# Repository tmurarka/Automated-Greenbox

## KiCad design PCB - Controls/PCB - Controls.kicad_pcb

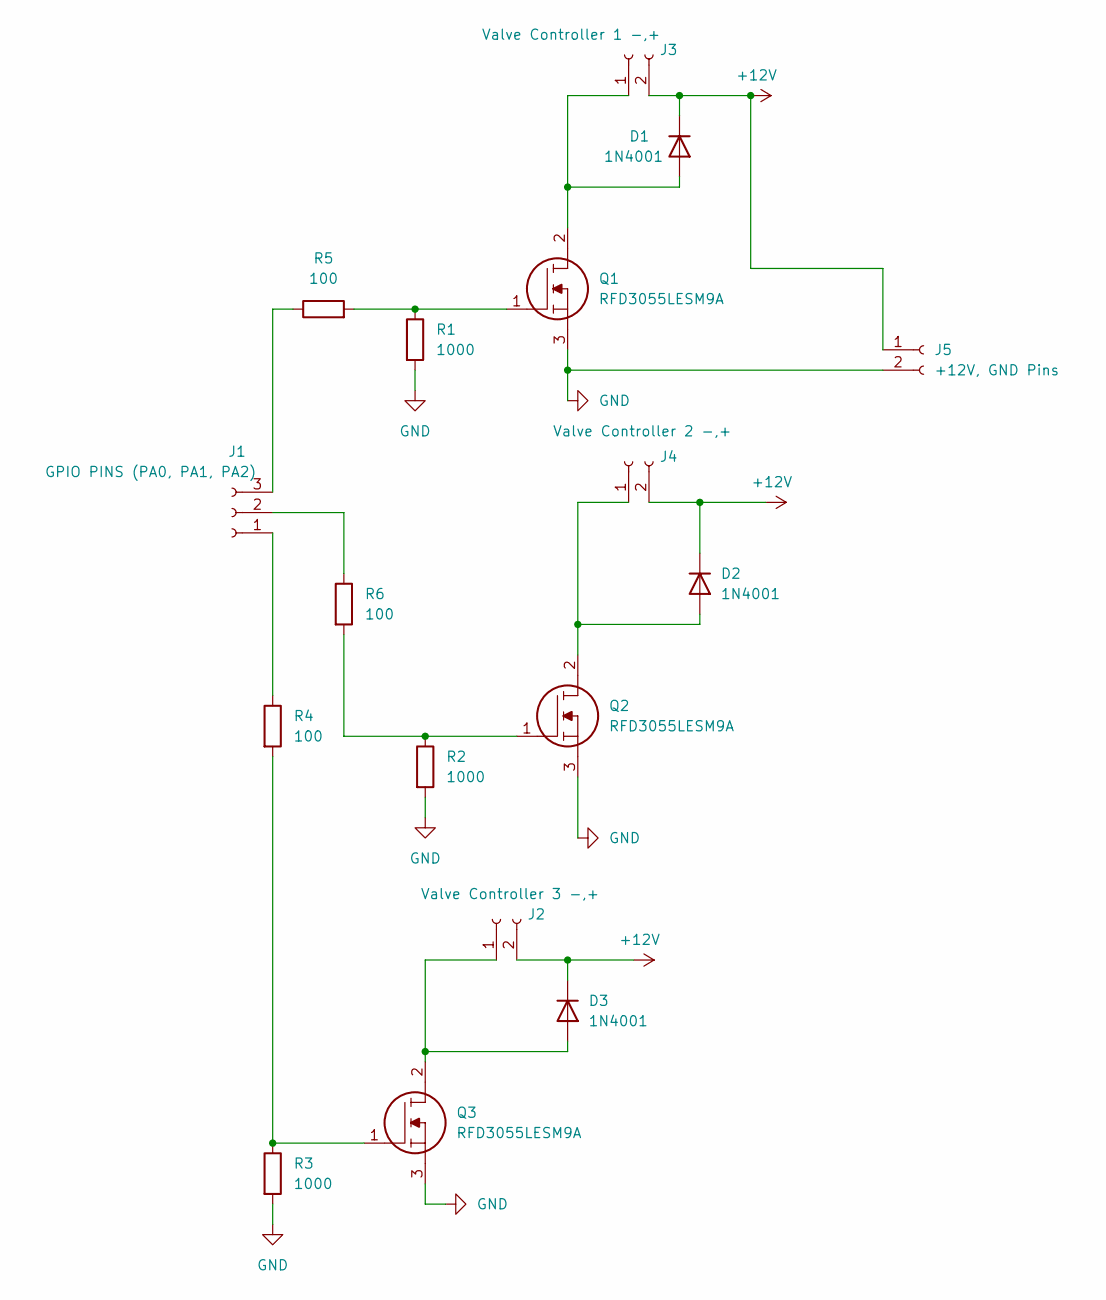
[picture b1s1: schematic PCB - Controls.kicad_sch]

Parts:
D1, D2, D3: 1N4001; D_DO-41_SOD81_P10.16mm_Horizontal
J1: GPIO PINS (PA0, PA1, PA2); PhoenixContact_MCV_1,5_3-G-3.81_1x03_P3.81mm_Vertical
J2: Valve Controller 3 -,+; PhoenixContact_MCV_1,5_2-G-3.81_1x02_P3.81mm_Vertical
J3: Valve Controller 1 -,+; PhoenixContact_MCV_1,5_2-G-3.81_1x02_P3.81mm_Vertical
J4: Valve Controller 2 -,+; PhoenixContact_MCV_1,5_2-G-3.81_1x02_P3.81mm_Vertical
J5: +12V, GND Pins; PhoenixContact_MCV_1,5_2-G-3.81_1x02_P3.81mm_Vertical
Q1, Q2, Q3: RFD3055LESM9A; FQD1N80TM; Mouser Part Number 512-RFD3055LESM9A
R1, R2, R3: 1000; R_Axial_DIN0204_L3.6mm_D1.6mm_P1.90mm_Vertical
R4, R5, R6: 100; R_Axial_DIN0204_L3.6mm_D1.6mm_P1.90mm_Vertical

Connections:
+12V: D1.1 (K), D2.1 (K), D3.1 (K), J2.2, J3.2, J4.2, J5.1
GND: J5.2, Q1.3, Q2.3, Q3.3, R1.2, R2.2, R3.2
unnamed: D1.2 (A), J3.1, Q1.2
unnamed: D2.2 (A), J4.1, Q2.2
unnamed: D3.2 (A), J2.1, Q3.2
unnamed: J1.1, R4.1
unnamed: J1.2, R6.1
unnamed: J1.3, R5.1
unnamed: Q1.1, R1.1, R5.2
unnamed: Q2.1, R2.1, R6.2
unnamed: Q3.1, R3.1, R4.2

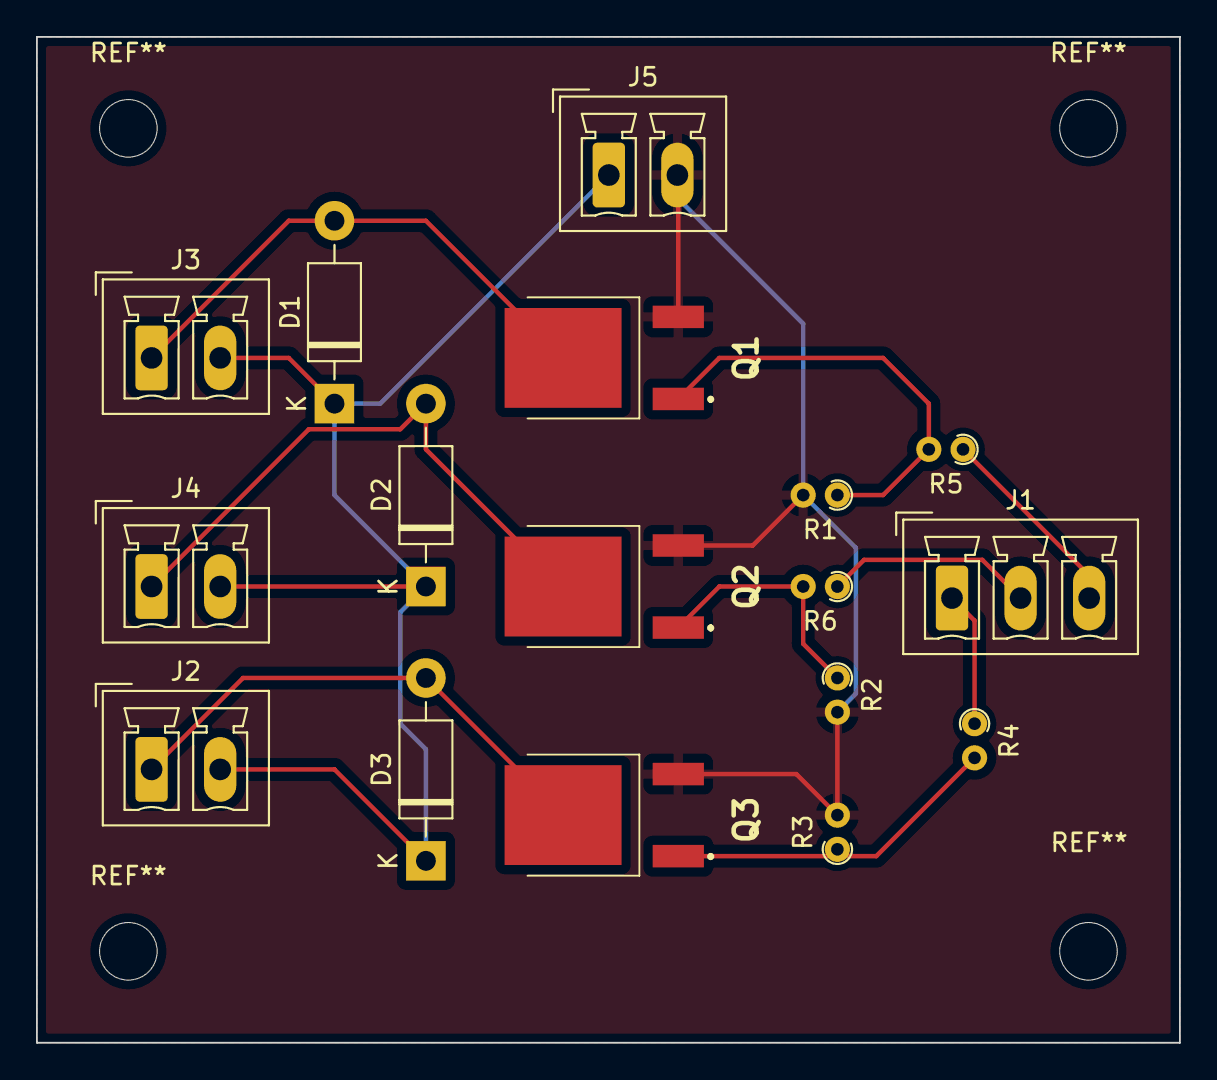
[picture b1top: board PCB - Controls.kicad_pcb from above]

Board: 2 copper layers, 63.5 x 55.9 mm, 17 parts (0 on the bottom side), 11 nets.

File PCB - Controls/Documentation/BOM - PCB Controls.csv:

"Source:","/Users/tmurarka/Library/Mobile Documents/com~apple~CloudDocs/Senior - Spring 2022/ECE 49022/PCB - Controls/PCB - Controls.kicad_sch"
"Date:","Wednesday, February 23, 2022 at 03:33:02 PM"
"Tool:","Eeschema (6.0.1-0)"
"Generator:","/Applications/KiCad.app/Contents/SharedSupport/plugins/bom_csv_grouped_by_value.py"
"Component Count:","19"

"Individual Components:"

"Item","Qty","Reference(s)","Value","LibPart","Footprint","Datasheet","Description","Height","Manufacturer_Name","Manufacturer_Part_Number","Mouser Part Number","Mouser Price/Stock"
"","","D1","1N4001","Diode:1N4001","Diode_THT:D_DO-41_SOD81_P10.16mm_Horizontal","http://www.vishay.com/docs/88503/1n4001.pdf","","","","","",""
"","","D2","1N4001","Diode:1N4001","Diode_THT:D_DO-41_SOD81_P10.16mm_Horizontal","http://www.vishay.com/docs/88503/1n4001.pdf","","","","","",""
"","","D3","1N4001","Diode:1N4001","Diode_THT:D_DO-41_SOD81_P10.16mm_Horizontal","http://www.vishay.com/docs/88503/1n4001.pdf","","","","","",""
"","","J1","Microcontroller GPIO Pins (PA0, PA1, PA2)","Connector:Conn_01x03_Female","Connector_PinHeader_2.54mm:PinHeader_1x03_P2.54mm_Vertical","~","","","","","",""
"","","J2","Valve Controller 1 (- Pin)","Connector:Conn_01x01_Female","Connector_PinHeader_2.54mm:PinHeader_1x01_P2.54mm_Vertical","~","","","","","",""
"","","J3","Valve Controller 2 (- Pin)","Connector:Conn_01x01_Female","Connector_PinHeader_2.54mm:PinHeader_1x01_P2.54mm_Vertical","~","","","","","",""
"","","J4","Valve Controller 3 (- Pin)","Connector:Conn_01x01_Female","Connector_PinHeader_2.54mm:PinHeader_1x01_P2.54mm_Vertical","~","","","","","",""
"","","J5","12 V","Connector:Conn_01x01_Female","Connector_PinHeader_2.54mm:PinHeader_1x01_P2.54mm_Vertical","~","","","","","",""
"","","J6","Valve Controller 1,2,3 (+ Pin)","Connector:Conn_01x03_Female","Connector_PinHeader_2.54mm:PinHeader_1x03_P2.54mm_Vertical","~","","","","","",""
"","","J8","GND","Connector:Conn_01x01_Female","Connector_PinHeader_2.54mm:PinHeader_1x01_P2.54mm_Vertical","~","","","","","",""
"","","Q1","RFD3055LESM9A","RFD3055LE:RFD3055LESM9A","RFD3055LE:FQD1N80TM","http://www.onsemi.com/pub/Collateral/RFD3055LESM-D.pdf","MOSFET, Fairchild, RFD3055LESM9A","2.39","ON Semiconductor","RFD3055LESM9A","512-RFD3055LESM9A","https://www.mouser.co.uk/ProductDetail/ON-Semiconductor-Fair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"
"","","Q2","RFD3055LESM9A","RFD3055LE:RFD3055LESM9A","RFD3055LE:FQD1N80TM","http://www.onsemi.com/pub/Collateral/RFD3055LESM-D.pdf","MOSFET, Fairchild, RFD3055LESM9A","2.39","ON Semiconductor","RFD3055LESM9A","512-RFD3055LESM9A","https://www.mouser.co.uk/ProductDetail/ON-Semiconductor-Fair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"
"","","Q3","RFD3055LESM9A","RFD3055LE:RFD3055LESM9A","RFD3055LE:FQD1N80TM","http://www.onsemi.com/pub/Collateral/RFD3055LESM-D.pdf","MOSFET, Fairchild, RFD3055LESM9A","2.39","ON Semiconductor","RFD3055LESM9A","512-RFD3055LESM9A","https://www.mouser.co.uk/ProductDetail/ON-Semiconductor-Fair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"
"","","R1","1000","Device:R","Resistor_THT:R_Axial_DIN0204_L3.6mm_D1.6mm_P1.90mm_Vertical","~","","","","","",""
"","","R2","1000","Device:R","Resistor_THT:R_Axial_DIN0204_L3.6mm_D1.6mm_P1.90mm_Vertical","~","","","","","",""
"","","R3","1000","Device:R","Resistor_THT:R_Axial_DIN0204_L3.6mm_D1.6mm_P1.90mm_Vertical","~","","","","","",""
"","","R4","100","Device:R","Resistor_THT:R_Axial_DIN0204_L3.6mm_D1.6mm_P1.90mm_Vertical","~","","","","","",""
"","","R5","100","Device:R","Resistor_THT:R_Axial_DIN0204_L3.6mm_D1.6mm_P1.90mm_Vertical","~","","","","","",""
"","","R6","100","Device:R","Resistor_THT:R_Axial_DIN0204_L3.6mm_D1.6mm_P1.90mm_Vertical","~","","","","","",""



"Collated Components:"

"Item","Qty","Reference(s)","Value","LibPart","Footprint","Datasheet","Description","Height","Manufacturer_Name","Manufacturer_Part_Number","Mouser Part Number","Mouser Price/Stock"
"1","3","D1, D2, D3","1N4001","Diode:1N4001","Diode_THT:D_DO-41_SOD81_P10.16mm_Horizontal","http://www.vishay.com/docs/88503/1n4001.pdf","","","","","",""
"2","1","J1","Microcontroller GPIO Pins (PA0, PA1, PA2)","Connector:Conn_01x03_Female","Connector_PinHeader_2.54mm:PinHeader_1x03_P2.54mm_Vertical","~","","","","","",""
"3","1","J2","Valve Controller 1 (- Pin)","Connector:Conn_01x01_Female","Connector_PinHeader_2.54mm:PinHeader_1x01_P2.54mm_Vertical","~","","","","","",""
"4","1","J3","Valve Controller 2 (- Pin)","Connector:Conn_01x01_Female","Connector_PinHeader_2.54mm:PinHeader_1x01_P2.54mm_Vertical","~","","","","","",""
"5","1","J4","Valve Controller 3 (- Pin)","Connector:Conn_01x01_Female","Connector_PinHeader_2.54mm:PinHeader_1x01_P2.54mm_Vertical","~","","","","","",""
"6","1","J5","12 V","Connector:Conn_01x01_Female","Connector_PinHeader_2.54mm:PinHeader_1x01_P2.54mm_Vertical","~","","","","","",""
"7","1","J6","Valve Controller 1,2,3 (+ Pin)","Connector:Conn_01x03_Female","Connector_PinHeader_2.54mm:PinHeader_1x03_P2.54mm_Vertical","~","","","","","",""
"8","1","J8","GND","Connector:Conn_01x01_Female","Connector_PinHeader_2.54mm:PinHeader_1x01_P2.54mm_Vertical","~","","","","","",""
"9","3","Q1, Q2, Q3","RFD3055LESM9A","RFD3055LE:RFD3055LESM9A","RFD3055LE:FQD1N80TM","http://www.onsemi.com/pub/Collateral/RFD3055LESM-D.pdf","MOSFET, Fairchild, RFD3055LESM9A","2.39","ON Semiconductor","RFD3055LESM9A","512-RFD3055LESM9A","https://www.mouser.co.uk/ProductDetail/ON-Semiconductor-Fair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"
"10","3","R1, R2, R3","1000","Device:R","Resistor_THT:R_Axial_DIN0204_L3.6mm_D1.6mm_P1.90mm_Vertical","~","","","","","",""
"11","3","R4, R5, R6","100","Device:R","Resistor_THT:R_Axial_DIN0204_L3.6mm_D1.6mm_P1.90mm_Vertical","~","","","","","",""

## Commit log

2022-11-08 Greenbox
